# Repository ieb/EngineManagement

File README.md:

# Engine Management 

In July 2021 my boat was hit by lightning. The Volvo Penta D2-40 MDI unit that manages the Engine, a Volvo Penta D2-40F failed badly leaving the starter motor engaged and nearly causing an engine fire.

# Main control board

Update 20240417: In service, no issues after 3 years.

(see pcb/EngineManagementSimpleWithRelays.sch )

This project is based on the standard wiring for the core engine which is a Perkins 100. In that form the engine is controlled by switches, relays and a few flyback diodes. The only part of the original engine control that survived the strike was the Volvo Penta buttons, so those are used by a control board with pnp transistors driving relays triggered by the original buttons pulling the base of the pnp to ground. PushOn/PushOff is provided by a latching relay unit based on a LED control chip that draws a few uA when off. The control circuit draws 0.5A max and is protected by a 5A fuse and 600W TVS which will blow the fuse in the event of a voltage surge.

The main relays for Start, Stop, Glow and aux are all standard iso 40A automotive relays, each circuit fused with a suitable fuse. 

There are basic alarms for oil pressure, charge and temperature with the temperature alarm using a differential op amp with high gain adjusted to turn on a pnp at a set temperature. These all drive a buzzer with LEDs to indicate the alarm. 

A standard Tachometer sensing from the alternator W+ provides rev and engine hours. These are almost disposable being 30 GBP on eBay from many sources, all 85mm same as the Volvo Penta Tachometer.

## Mosfet alternative

Update 20240417: The PCB was prototyped, but never put into service since the relay based control board has proved 100% reliable and in service for 3 years. This section is for reference.

Although the original MDI failed due to the MOSFETs going short circuit, and in this respect relays may be more robust, it should be possible to protect MOSFETs or at least fail safe.

A 1.5KW TVS (eg SMCJ14A) with a 14.0V revers standoff, 15.6V minimum breakdown will conduct 5A@16V, 10A@18V and 40A@20V, which makes it viable as protection for excessive voltages upto 40A current, aiming to blow a fuse at above those voltages. Each mosfet needs its own TVS + suitably sized fuse or breaker. In the event of a strike or surge the TVS will short and blow the fuse before damage is done even if the MOSFET is shorted. It wont work for currents greater than 40A without exceeding the max Vds voltage of the MOSFET below.

A SI7137DP-T1-GE3 has an on resistance of 0.0016 Ohms and will dissipate < 640mW for 20A when fully on. It, unfortunately has a Max Vds of 20V and Vgs of 12v so needs protection, but provided its protected represents a robust solution as a high level switch. 

In the relay board on/off was provided by a eBay relay board which used a LED controller. To keep the number of daughter boards to a minimum and save space this is replaced by a MAX15054 on-off controller driving a N-Channel mosfet which when turned on draws the gate of one of the SI7137's to near zero turning it fully on. The same N-Channel mosfet enables P-Channel mosfets connected to the gates of other SI7137s. When the VP buttons are pressed the gates of these mosfets are dragged down to 0v turning them on, and since the N-Channel mosfet is conducting the gate of the respective SI7137 is also dragged to 0v switching that mosfet on. All P-Channel gates are pulled to +ve, and all N-Channel gates are pulled to 0v. The SI7137 has a max source gate voltage of 12v and so a 10v zener with forward diode ensures that never gets over 11.5v. 

Simulations indicate that the power dissipation in the SI7137 at 20A is 2.5W, so a pair are used for the glow plugs. At 8A for the start and stop solenoids power dissipation is closer to 500mW. Board cooling pads are used, although it might be necessary to add chip heat sinks.

Since the SI7137 are 1/10th the size of the relays, the switching circuit and NMEA2000 interface controller will all fit onto a single 10cm x 15cm board (which is the size I have in stock).

All of the silicon components were available at Farnell except the SI7137's which were ordered from Mouser, airmailed from California. For some reason RS in the UK had no stock of any mosfets.

see pcb/EngineManagementWithMosfets.sch which includes a sub-sheet of the NMEA interface. There are LTSpice simulations in pcb/simulations/ of the mosfet layout confirming transient behavior, currents and power dissipation.

Since its likely that when there is a voltage spike something on the board will blow, assuming this board works, I'll probably make a batch and keep a few spares onboard the boat.

# NMEA2000 Interface

Update 20240417: In service, minor issues after 3 years, mostly surrounding message frequency and how to some parameters to display on standard instruments.

(see pcb/EngineManagement.sch)

The standard MDI talks J1939 which is the Diesel engine CAN standard protocol. Normally this communicates with other Volvo Penta instruments, but in my case this was only the Tachometer. The J1939 Volvo Penta Tachometer did not survive the strike. The CAN bus interface was destroyed, even though there was an attempt to protect if from surges. At over 500 GBP to replace, I decided to stick with the non J1939 tachometer from eBay. For details on how to drive J1939 see the main_deprecated.cpp file. Volvo Penta service technicians probably query the MDI for fault codes, but for owners there is limited benefit where the only unit is a tachometer or basic instruments.

Once I discovered the VP Tachometer was not repairable, a separate mechanical diesel to NMEA2000 board was designed and built around an Arduino Pro Mini (Atmel 328p MCU), MCP2515 CAN controller board and some passive components. There is just enough space on 328p to hold the code and run the controller and the data collected and emitted can be displayed on any NMEA2000 instrument (eg Raymarine e7 MFD).

Component cost of the boards is probably less than 30 GBP, hence spares boards can be carried and in the worst case the engine can be controlled manually.

Replacing the blown VP parts with OEM parts would have been 1500 GBP with a further 1500 GBP required for the spare set, safe in the knowledge that a EM pulse from a near strike would result in precisely the same failure and risk of engine fire.

## NMEA2000 Messages

A D-2/40 is not exactly performance. Its not going to rev up quickly and so periods of 100ms are not really necessary for rapid engine. Same with temperatures which are really not going to change that fast. 5s is plenty fast enough.  10s is too long and most instruments treat this as no data sent.

* pgn 127488 rapid engine, 500ms
* pgn 127489 dynamic engine 1s  oil temperature == alternator temperature.
* pgn 127505 tank level 5s, instance 0 fuel type 0 diesel 
* pgn 130316 temperatures 5s,  instance/source 0/14=Exhaust, 1/3=EngineRoom, 2/15=Alternator.
* pgn 127508L battery voltage 1s, instance 0=engine battery, voltage only. instance 2=Alternator, voltage and temperature

The main battery as its now LiFePO4 with a serial to BLE module providing very detailed information. A CAN interface to this could be implemented, but the standard android app gives more than enough information and is lower power.  The original battery sensor mechanism didnt work well due to slight differences in -ve potential at the battery terminals. Hence the N2K interface only monitors Engine Battery and Alternator voltages. With a LiFeP04 battery, alternator temperature has become more important. Alternator load is controld via a Sterling A2B 120A converter which actively monitors and protect the alternator from excessive load.

# Sensors

The standard  VP flywheel pickup produces 415Hz 20V pk2pk puses with sharp edges at idle, however the signal is noisy and so it needs to be conditioned. A Schmidt trigger using an OpAmp set up positive feedback to reduce hysteresis. The positive input uses a RC network acting as a low pass filter reducing the sensitivity as the rpm rises, eliminating high frequencies ( > 10KHz). On the negative a RC network smooths the input voltage to find the mean allowing automatic offset compensation. The time period constant of the -ve input is >> than the +ve.  The inputs are via 22K resistors with the voltage measured over 100K. There are 2 chopper diodes to limit the input voltage to no more than 1V.

Using a 358 opamp with 5V supply the square wave out is 3.7V high and 0.7v low, which is just enough (3.5v being logic high), 1.5 below Vcc isn't great for an OpAmp, however 3v is high on an Arduino.

The frequency is measured by timing 10 pulses using micros().

The previous attempt without a Schmidt Trigger failed to work reliably due to noise.

The standard VP oil pressure switch is a simple switch that closes when the oil pressure drops below a threshold.

The standard VP coolant temperature sensor is identical to almost every other coolant sensor, with about 1743R at 0C and 22R at 120C. When about 33R (105C adjustable) is measured the alarm is triggered.

The charge alarm uses the voltage across the resistor supplying current into the alternator excitation coil, analogous to the charge light in cars long before there were computers.

The NMEA2000 interface board also measures fule level (0R-190R), battery voltage, alternator voltage, and 3 NCT inputs. Inputs are protected with capacitors and 100K resistors to limit current.

# Outputs

The relay board provides outputs for starter motor, stop solenoid, glow plugs and aux 12v.

The NMEA2000 board provides NMEA2000 messages.

# Connections.

The VP wiring loom has largely been replaced except for the connection to the VP buttons. Most of the original wiring loom was melted by the starter motor, but the rest was strapped tightly to the engine risking shorts when it melted.

The control box will be mounted outside the engine bay where temperatures are considerably lower (typically < 30C vs often > 85C next to the engine).

# Code

Code is all in main.cpp rather than a classes since there is little to it and I needed tight control over memory usage (less risk of hidden bloat). NMEA support uses 

	https://github.com/ttlappalainen/NMEA2000.git
	https://github.com/ttlappalainen/NMEA2000_mcp.git
	https://github.com/ttlappalainen/CAN_BUS_Shield.git

however there are some patches required, see src/*.patch. 
src/CAN_BUS_Shield.patch. The SPI clk was heavily distorted at 8MHz with a Pro Mini so I dropped the SPI to 1MHz to get a clean clk square wave. 

src/NMEA2000-library.patch The memory savings (see NMEA2000_CompilerDefns.h) which are required to run on a 382p dont compile without this patch. Additionally there I needed feedback on serial of failed packets without enabling all packet output.

Both patches must be applied if pulling fresh dependencies. 

# Memory usage

Building .pio/build/pro16MHzatmega328/firmware.hex
Advanced Memory Usage is available via "PlatformIO Home > Project Inspect"
RAM:   [==        ]  18.4% (used 377 bytes from 2048 bytes)
Flash: [========= ]  89.4% (used 27458 bytes from 30720 bytes)

If debugging of the sensors is enabled, then NMEA2000 output may have to be disabled to get the code to fit into FLASH. No problems seen with RAM at the moment, but it hasnt been tested on a live NMEA2000 bus yet.

## Update on memory.

Memory usage has proved a problem. The NMEA2000 library was designed for chips with more memory than a Pro mini and although it will run, it runs out of stack and heap when dealing with ISO Reqeusts, causing the cpu to lock up or crash. It is possible to greatly reduce memory usage by limiting buffer sizes but this truncates the responses ot the ISO requests. I think the underlying problem is that the NMEA2000 library uses temporary buffers allow it to use interrupts and to support TP packets.

So, the code is now switched to a smaller SNMEA2000 library. This only uses an 8 byte buffer for sending and is written to load that buffer, sending when full. It supports standard packets and fast packet messages. It doesn't support interrupts and is a lot simpler. 

Building with debug enabled all in ram gives
RAM:   [===       ]  32.2% (used 659 bytes from 2048 bytes)
Flash: [====      ]  37.4% (used 11492 bytes from 30720 bytes)

Initial tests indicate 1292 bytes ram available at all times when running, compared to the < 60 bytes reported with the smallest viable NMEA2000 configuration. Most of the implementation is informed by the NMEA2000 code and functionality for each use is by extension only. To reduce the work load on a polling only interface to the MCP2515 message filters are implemented on receive. It only supports a MCP2515 over SPI and will only run on an AVR based chip as it assumes little endian.

The code has, or is being verified talking to a ESP32 + MCP2562 running the NMEA2000 device analyzer.

# Changes

* 20240417  Reduced the periods for battery and fuel to 5s from 10s as N2K instruments were showing -.- periodically.
* 20240417  Output Alternator temperature to Engine Oil Temp and a dedicated "battery" (no 2) for display. Oddly no standard PGN for an DC alternator available.

# Todo/Status Relay Board

[x] Build prototype PCB and populate.
[x] Test on/off sequence.
[x] Test 20x4 I2C display.
[x] Test port extender. - discovered Can board back powers 5v switched line, added blocking diode.
[x] Connect 8 way relay board and test.
[x] Verify CAN board working.
[ ] Connect test harness sensors and test.
[FAIL] Connect VP Taco and test with simulated engine - the VP Taco is blown internally, CanH at 5V, CanL and 0V. Inside three is a large Asic which looks like it directly controls the Can bus. Very unlikely to be 
able to repair. Google for the numbers turns up no chips, and none of the other chips are CAN related.

[x] Design build and test simple relay controller unit with no MCU
[x] Design build NMEA2000 controller board
[x] Test NCT readings,  - adjusted to 4.7K top R and rebuilt NTC table from base equations.
[x] Test coolant readings - tested with fake NTC sensor wiring, need full test on real sensor
[x] Test fuel level readings
[x] Test voltage readings
[x] Test coolant with variable voltage.
[x] Test RPM with signal generator
[x] Test NMEA2000 output
[x] install
[x] Test output on MFD, all working except Charge alarm sounds all the time and RPM sensor is unreliable.
[x] Fix RPM sensor, using Schmidt trigger
[x] (disabled) Fix charge sensor, adjust resistors or disable.
[x] Adjust temperature sensor
[x] calibrate ADCs, or at least check they are correct.
[x] Test again.
[x] Install check RPM with strobe
[x] Fix fuel and voltage periods, 10s too long for N2K instruments, dropped to 5s.
[x] Output alternator temperature as oil temp, dedicated "battery" instance 2.

# Todo Status Mosfet board

This has been put on hold as the relay board works well other than the charge and temperature alarms whcih are too sensitive. Same mosfets have been used for a high current remote switch and appear to produce almost zero heat dissipation.

[x] Simulate everything in LTSpice
[x] Layout PCB
[ ] Mill prototype
[x] Order Silicon
[ ] Build prototype
[ ] Test on/off
[ ] Test other buttons and circuits, under load ideally.
[ ] Test warning circuits
[ ] Test sensors
[ ] Test NMEA2000 output
[ ] Install
[ ] Test running
[ ] Order boards and build spares.

# CanDrivers

# AVR -> MCP2515 -> TJA1050

TJA1050 runs on 5V but can take 3 or 5v logic in.
MCP2515 will run on 3v or 5v On 3v it will need a 1K/10K divider to take TJA1050 out from 3.6v to 3.3v

Scope output for this setup on 5V is very clean

# ESP -> TJA1050

TJA1050 runs on 5v with a divider on RX out to take Vrxh to 3.3v, may be easier than a MCP2562, although the output from a MCP2562 is not nearly as clean.

This setup works. Output is very clean, however the mean voltage is sensitive to the 5V supply being exactly 5V.

# Pi -> MCP2515 -> TA1050

Same as 3v AVR 3v.
Would also need a RTC, DS3231  with a LI charger TP4056
Not done as was able to fit everything I wanted into a ESP32 running a http server which draws < 40mA when not transmitting on WiFi, see CanDiagnose project.

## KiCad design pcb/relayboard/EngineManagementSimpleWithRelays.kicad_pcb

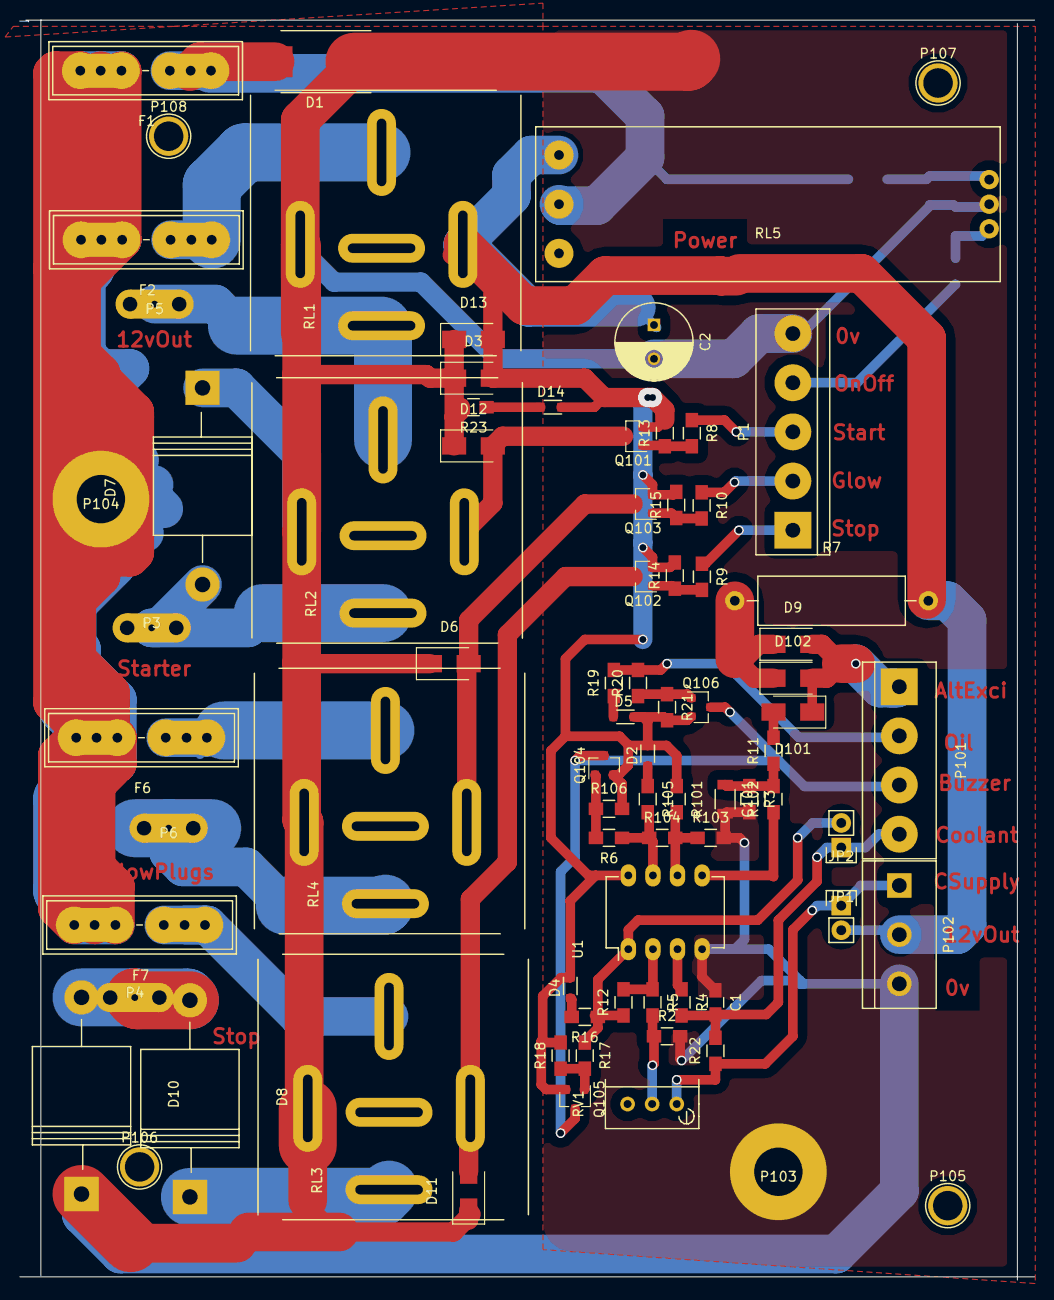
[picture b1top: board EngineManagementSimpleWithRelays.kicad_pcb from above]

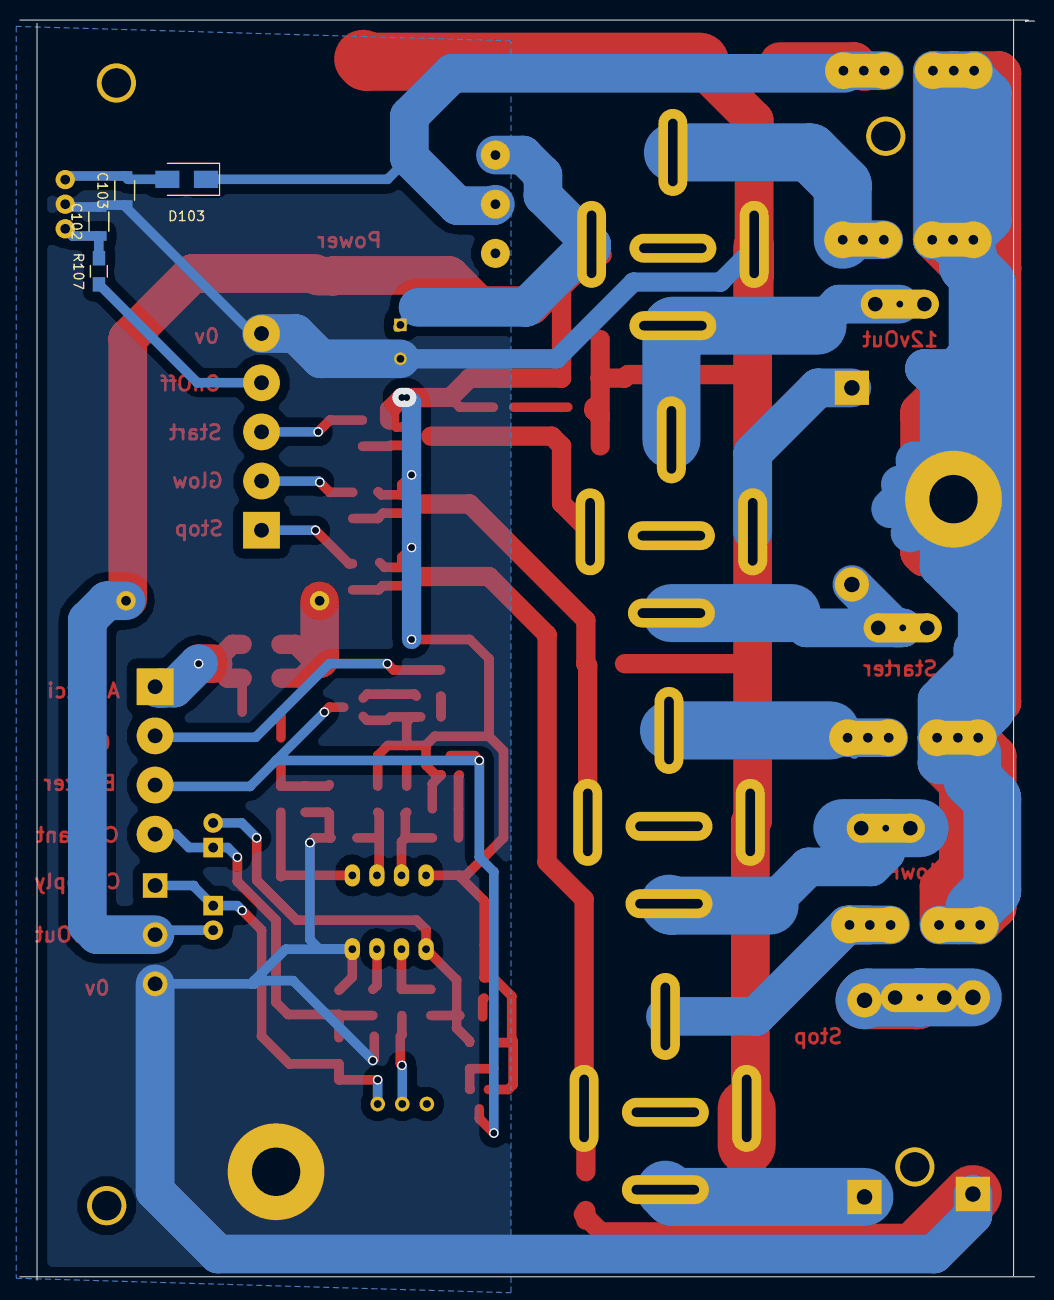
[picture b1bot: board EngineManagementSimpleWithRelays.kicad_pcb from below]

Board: 2 copper layers, 104.8 x 130.2 mm, 83 parts (4 on the bottom side), 46 nets.

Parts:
C1: 10nF; C_0805_HandSoldering
C2: 100uF; C_Radial_D8_L11.5_P3.5
C101, C103: 1uF; C_1206
C102: 100nF; C_1206
D1: SMBJ30CA-TR TSV; DO-214AB_Handsoldering
D2: ChargeWarn; D_0805
D3, D9, D102, D103: S1JL 1A 40V; D_SMA_Standard
D4: TempWarn; D_0805
D5, D14: OilWarn; D_0805
D6, D11, D12, D13: S1JL 1A 600V; D_SMA_Standard
D7: 5A 600V; Diode_P600_Horizontal
D8, D10: 10A 600V; Diode_P600_Horizontal
D101: SlJL 1A 40V; D_SMA_Standard
F1: FUSE 5A; BladeFuse-CarType
F2, F6: FUSE 30A; BladeFuse-CarType
F7: FUSE 15A; BladeFuse-CarType
JP1: UseSensorAlarm; Pin_Header_Straight_1x02
JP2: Use12vSupply; Pin_Header_Straight_1x02
P1: VPButtons; bornier5
P3: StarterSolenoidT30; CrimpBlade
P4: StopSolenoid; CrimpBlade
P5: 12VSwitchedPower; CrimpBlade
P6: GlowPlugs; CrimpBlade
P101: CONN_4; bornier4
P102: CONN_3; bornier3
P103: 0v; M5Bolt
P104: Battery+; M5Bolt
P105, P106, P107, P108: mount; 1pin
Q101, Q102, Q103, Q104, Q105, Q106: BC807-40; SOT-23
R2: 330R; R_0805_HandSoldering
R3: 1M; R_0805_HandSoldering
R4, R5, R6, R13, R14, R15, R17, R21, R101: 10K; R_0805_HandSoldering
R7: 10R; Resistor_Horizontal_RM20mm
R8, R9, R10, R18, R20, R106: 2.2K; R_0805_HandSoldering
R11, R16, R19, R22, R23, R102, R105, R107: 1K; R_0805_HandSoldering
R12: 10M; R_0805_HandSoldering
R103: 22K; R_0805_HandSoldering
R104: 100K; R_0805_HandSoldering
RL1: EnginePower; AutomotiveRelay35A
RL2: EngineStart; AutomotiveRelay35A
RL3: EngineStop; AutomotiveRelay35A
RL4: GlowPlugs; AutomotiveRelay35A
RL5: LatchingRelay
RV1: 10K; Potentiometer_Bourns_3296W_3-8Zoll_Inline_ScrewUp
U1: LM358; DIP-8_W7.62mm_LongPads

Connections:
12vSwitched: C2.1, D2.1, D3.2, D4.1, D5.1, D13.2, D14.1, JP2.2, P102.2, Q101.2, Q102.2, Q103.2, Q104.2, Q105.2, Q106.2, R7.2, R13.2, R14.2, R15.2, R18.2, R21.2, R101.1, R106.2, RL1.86, RL5.6, U1.8
AlternatorExcitation: D9.2, D101.1, D102.2, P101.1
Battery+: F1.2, F2.2, F6.2, F7.2, P104.1
BatteryFused5A: D1.2, D103.1, F1.1, RL5.4
Buzzer: P101.3, Q104.3, Q105.3, Q106.3
CoolantSensorSupply: JP2.1, P102.1, R22.1, RV1.1
CoolantTemp: C1.2, JP1.1, P101.4, R4.2, R22.2
GND: C1.1, C2.2, C101.2, C102.2, C103.1, D1.1, D3.1, D6.1, D7.1, D10.1, D11.1, D12.1, D13.1, P1.5, P102.3, P103.1, R2.2, R3.2, R23.2, R103.2, RL1.85, RL2.85, RL3.85, RL4.85, RL5.3, U1.4
GlowBtn: P1.2, R10.1
GlowCoil: D6.2, Q103.3, RL4.86
GlowPlugs: P6.1, RL4.87
unnamed: C101.1, R3.1, R11.1, R102.2
unnamed: C102.1, R107.2, RL5.2
unnamed: C103.2, D103.2, RL5.1
unnamed: D2.2, R105.1
unnamed: D4.2, R16.2
unnamed: D5.2, R19.1
unnamed: D8.1, RL3.87
unnamed: D14.2, R23.1
unnamed: D101.2, R11.2
unnamed: D9.1, D102.1, R7.1
unnamed: F2.1, RL1.30
unnamed: P5.1, RL1.87, RL2.30
unnamed: F6.1, RL4.30
unnamed: F7.1, RL3.30
unnamed: JP1.2, R12.1, R16.1, R17.1, U1.1
unnamed: Q101.1, R8.2, R13.1
unnamed: Q102.1, R9.2, R14.1
unnamed: Q103.1, R10.2, R15.1
unnamed: Q104.1, R6.2, R106.1
unnamed: Q105.1, R17.2, R18.1
unnamed: Q106.1, R20.1, R21.1
unnamed: R2.1, R5.2, RV1.2
unnamed: R4.1, U1.3
unnamed: R5.1, R12.2, U1.2
unnamed: R101.2, R103.1, R104.2, U1.6
unnamed: R102.1, U1.5
unnamed: R6.1, R104.1, R105.2, U1.7
OilSwitch: P101.2, R19.2, R20.2
OnOffBtn: P1.4, R107.1
StartBtn: P1.3, R8.1
StartCoil: D12.2, Q101.3, RL2.86
StarterSolenoidT30: D7.2, P3.1, RL2.87
StopBtn: P1.1, R9.1
StopCoil: D11.2, Q102.3, RL3.86
StopSolenoid: D8.2, D10.2, P4.1

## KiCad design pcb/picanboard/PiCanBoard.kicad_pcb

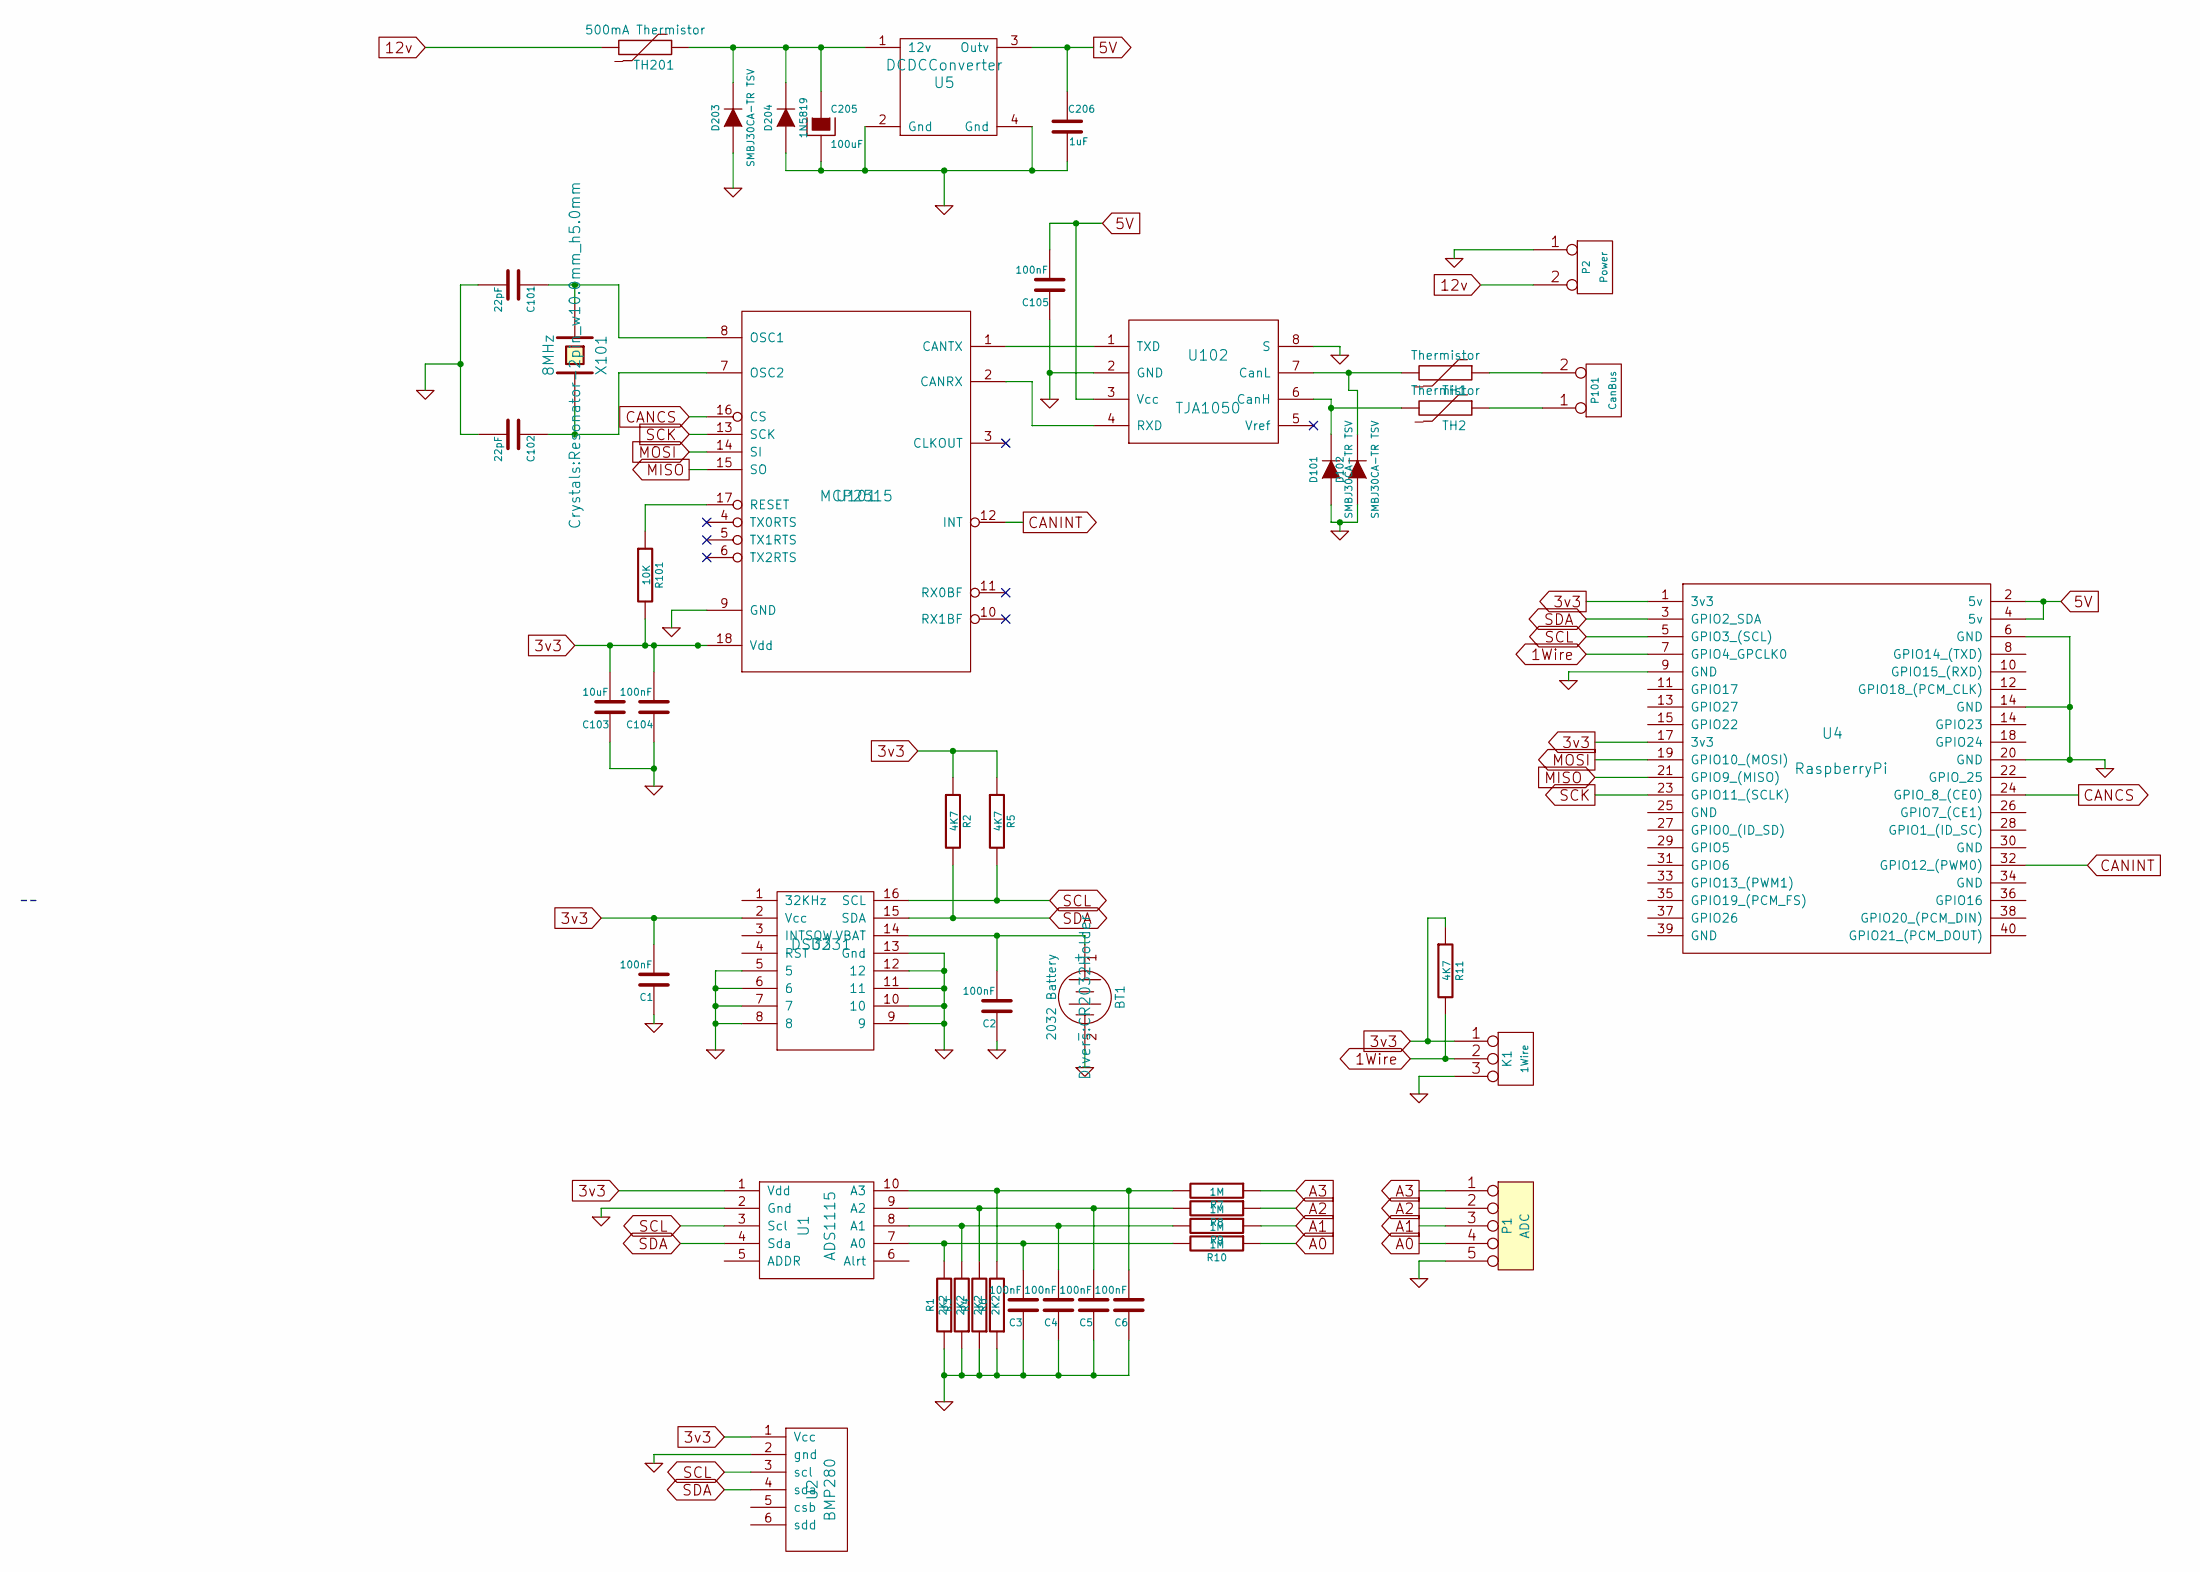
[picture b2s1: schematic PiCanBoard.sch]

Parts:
BT1: 2032 Battery; CR2032Holder
C1, C2, C3, C4, C5, C6, C104, C105: 100nF; C_0805_HandSoldering
C101, C102: 22pF; R_0603_HandSoldering
C103: 10uF; R_1206_HandSoldering
C205: 100uF; C_1210_HandSoldering
C206: 1uF; C_1210_HandSoldering
D101, D102, D203: SMBJ30CA-TR TSV; DO-214AB_Handsoldering
D204: 1N5819; DO-214AB_Handsoldering
K1: 1Wire; bornier3
P1: ADC; bornier5
P2: Power; bornier2
P101: CanBus; bornier2
R1, R3, R4, R6: 2K2; R_0805_HandSoldering
R2, R5, R11: 4K7; R_0805_HandSoldering
R7, R8, R9, R10: 1M; R_0805_HandSoldering
R101: 10K; R_0805_HandSoldering
TH1, TH2: Thermistor; R_1210
TH201: 500mA Thermistor; Resistor_Horizontal_RM7mm
U1: ADS1115
U2: BMP280
U3: DS3231; SOIC-16W_7.5x10.3mm_Pitch1.27mm
U4: RaspberryPi; PiZeroW
U5: DCDCConverter; DC-DC-Converter
U101: MCP2515; SOIC-18W_7.5x11.6mm_Pitch1.27mm
U102: TJA1050; SOIC-8_3.9x4.9mm_Pitch1.27mm
X101: 8MHz; Resonator-2pin_w10.0mm_h5.0mm

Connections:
1Wire: K1.2 (PM), R11.2, U4.7 (GPIO4_GPCLK0)
3v3: C1.2, C103.2, C104.2, K1.1, R2.1, R5.1, R11.1, R101.2, U1.1 (Vdd), U2.1 (Vcc), U3.2 (Vcc), U4.1 (3v3), U4.17 (3v3), U101.18 (Vdd)
5V: C105.2, C206.1, U4.2 (5v), U4.4 (5v), U5.3 (Outv), U102.3 (Vcc)
12v: P2.2 (PM), TH201.2
A0: P1.4, R10.1
A1: P1.3, R9.1
A2: P1.2, R8.1
A3: P1.1, R7.1
CANCS: U4.24 (GPIO_8_(CE0)), U101.16 (CS)
CANINT: U4.32 (GPIO12_(PWM0)), U101.12 (INT)
GND: BT1.2 (-), C1.1, C2.1, C3.1, C4.1, C5.1, C6.1, C101.2, C102.2, C103.1, C104.1, C105.1, C205.2, C206.2, D101.1 (A), D102.1 (A), D203.1 (A), D204.1 (A), K1.3, P1.5, P2.1, R1.1, R3.1, R4.1, R6.1, U1.2 (Gnd), U2.2 (gnd), U3.5, U3.6, U3.7, U3.8, U3.9, U3.10, U3.11, U3.12, U3.13 (Gnd), U4.6 (GND), U4.9 (GND), U4.14 (GND), U4.20 (GND), U5.2 (Gnd), U5.4 (Gnd), U101.9 (GND), U102.2 (GND), U102.8 (S)
MISO: U4.21 (GPIO9_(MISO)), U101.15 (SO)
MOSI: U4.19 (GPIO10_(MOSI)), U101.14 (SI)
unnamed: BT1.1 (+), C2.2, U3.14 (VBAT)
unnamed: C3.2, R1.2, R10.2, U1.7 (A0)
unnamed: C4.2, R3.2, R9.2, U1.8 (A1)
unnamed: C5.2, R4.2, R8.2, U1.9 (A2)
unnamed: C6.2, R6.2, R7.2, U1.10 (A3)
unnamed: C101.1, U101.8 (OSC1), X101.1
unnamed: C102.1, U101.7 (OSC2), X101.2
unnamed: C205.1, D203.2 (K), D204.2 (K), TH201.1, U5.1 (12v)
unnamed: D101.2 (K), TH2.2, U102.6 (CanH)
unnamed: D102.2 (K), TH1.2, U102.7 (CanL)
unnamed: P101.1, TH2.1
unnamed: P101.2 (PM), TH1.1
unnamed: R101.1, U101.17 (RESET)
unnamed: U101.1 (CANTX), U102.1 (TXD)
unnamed: U101.2 (CANRX), U102.4 (RXD)
SCK: U4.23 (GPIO11_(SCLK)), U101.13 (SCK)
SCL: R5.2, U1.3 (Scl), U2.3 (scl), U3.16 (SCL), U4.5 (GPIO3_(SCL))
SDA: R2.2, U1.4 (Sda), U2.4 (sda), U3.15 (SDA), U4.3 (GPIO2_SDA)

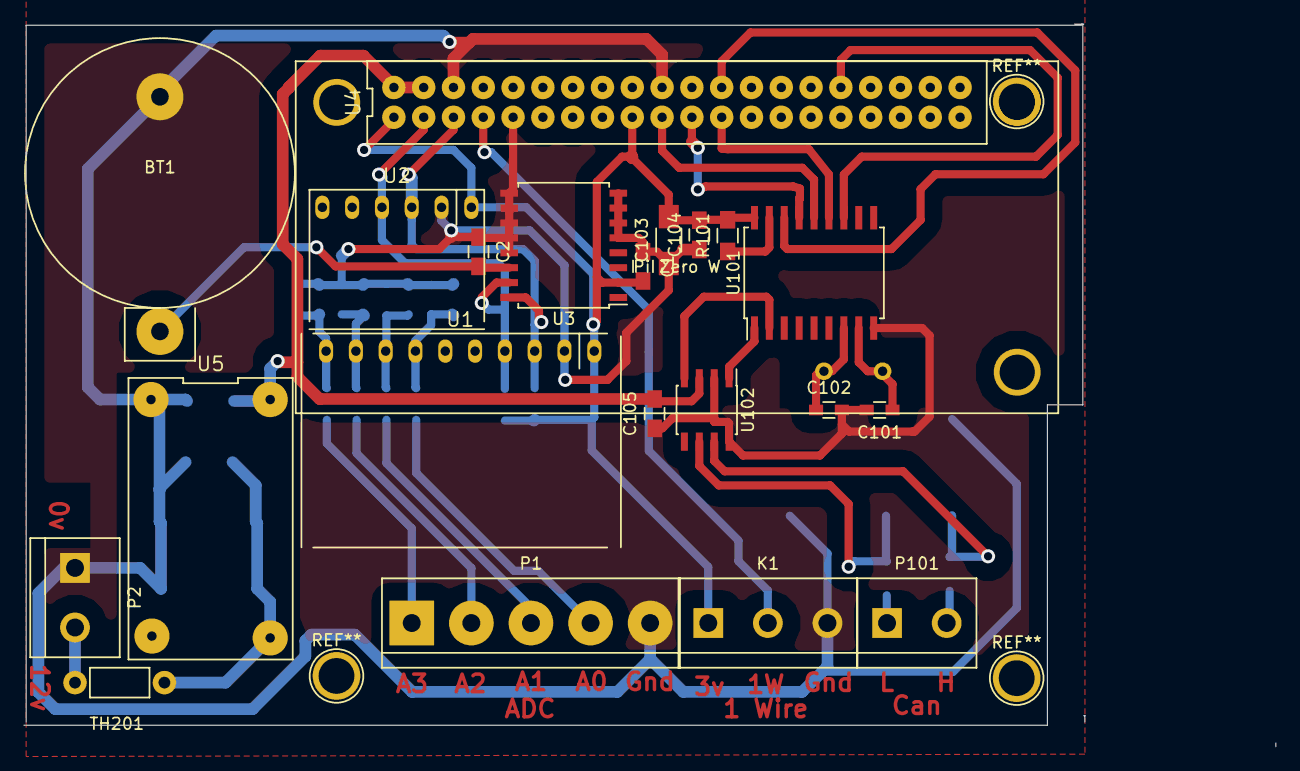
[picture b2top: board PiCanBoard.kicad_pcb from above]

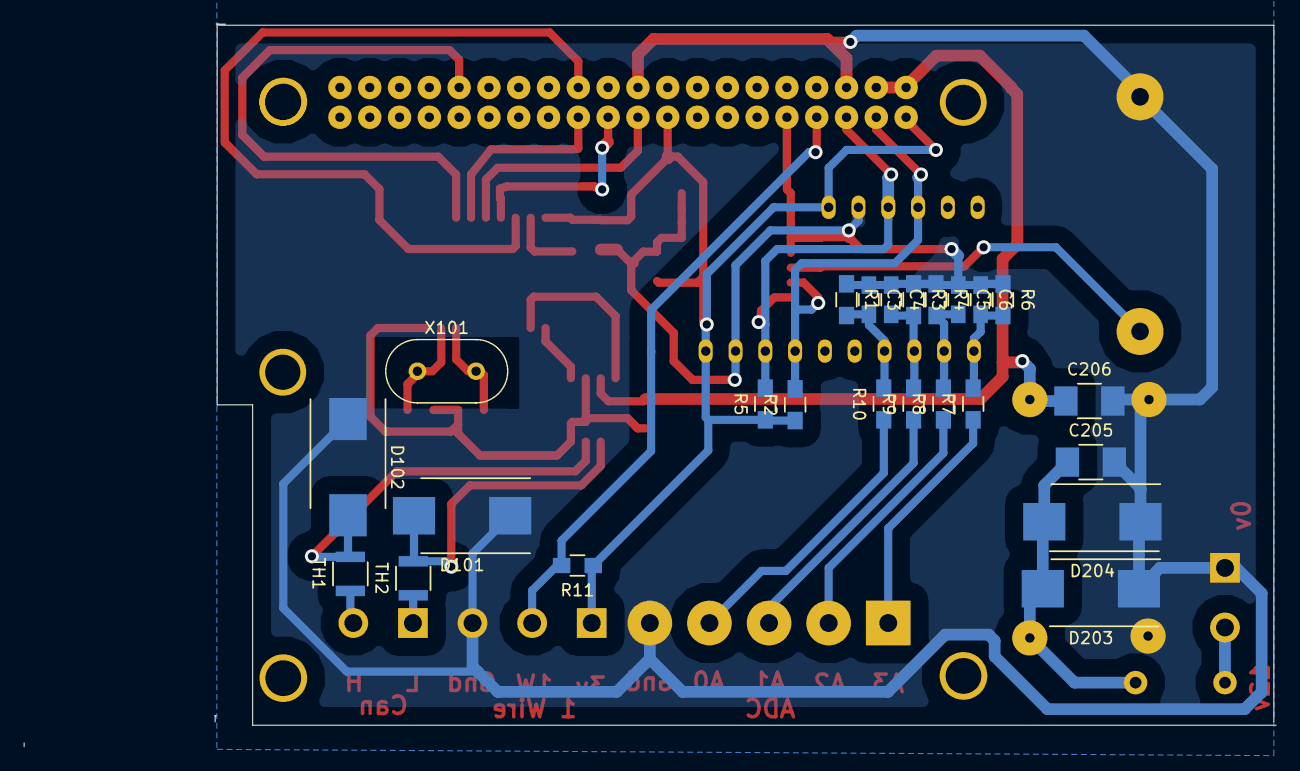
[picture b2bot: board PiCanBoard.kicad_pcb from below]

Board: 2 copper layers, 106.7 x 61.6 mm, 45 parts (24 on the bottom side), 31 nets.

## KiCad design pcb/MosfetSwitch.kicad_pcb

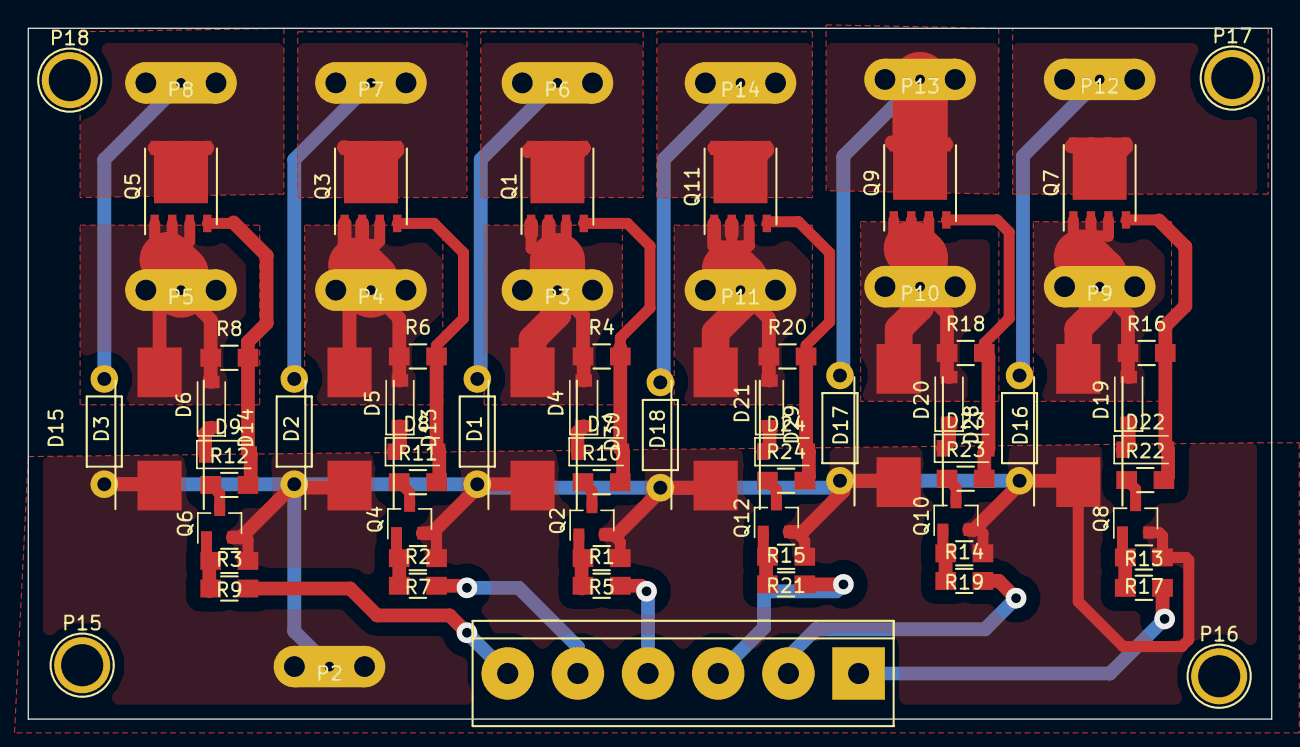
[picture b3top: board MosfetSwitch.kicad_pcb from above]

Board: 2 copper layers, 90.0 x 50.0 mm, 78 parts (0 on the bottom side), 43 nets.

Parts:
D1, D2, D3, D16, D17, D18: SMBJ30CA-TR TSV; DO-214AB_Handsoldering
D4, D5, D6, D19, D20, D21: ZENER; D_SOD-123
D7, D8, D9, D22, D23, D24: 1N4001; D_SOD-123
D13, D14, D15, D28, D29, D30: 1N4001; Resistor_Horizontal_RM7mm
P1: ToSwitches; bornier6
P2: 0v; CrimpBlade
P3: CH3In; CrimpBlade
P4: CH2In; CrimpBlade
P5: CH1In; CrimpBlade
P6: Ch3Out; CrimpBlade
P7: Ch2Out; CrimpBlade
P8: Ch1Out; CrimpBlade
P9: CH6In; CrimpBlade
P10: CH5In; CrimpBlade
P11: CH4In; CrimpBlade
P12: Ch6Out; CrimpBlade
P13: Ch5Out; CrimpBlade
P14: Ch4Out; CrimpBlade
P15, P16, P17, P18: hole; 1pin
Q1, Q3, Q5, Q7, Q9, Q11: SI7137; Si7137PowerPak
Q2, Q4, Q6, Q8, Q10, Q12: BC817-40; SOT-23
R1, R2, R3, R4, R5, R6, R7, R8, R9, R13, R14, R15, R16, R17, R18, R19, R20, R21: 10K; R_0805_HandSoldering
R10, R11, R12, R22, R23, R24: 470R; R_0805_HandSoldering

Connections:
CH1_SWITCH: P1.6, R3.2
CH2_SWITCH: P1.5, R2.2
CH3_SWITCH: P1.4, R1.2
CH4_SWITCH: P1.3, R15.2
CH5_SWITCH: P1.2, R14.2
CH6_SWITCH: P1.1, R13.2
GND: D1.1, D2.1, D3.1, D13.1, D14.1, D15.1, D16.1, D17.1, D18.1, D28.1, D29.1, D30.1, P2.1, Q2.2, Q4.2, Q6.2, Q8.2, Q10.2, Q12.2, R5.1, R7.1, R9.1, R17.1, R19.1, R21.1
unnamed: D1.2, D4.2, P3.1, Q1.2, R4.1
unnamed: D2.2, D5.2, P4.1, Q3.2, R6.1
unnamed: D3.2, D6.2, P5.1, Q5.2, R8.1
unnamed: D4.1, D7.1
unnamed: D5.1, D8.1
unnamed: D6.1, D9.1
unnamed: D7.2, Q1.1, R4.2, R10.2
unnamed: D8.2, Q3.1, R6.2, R11.2
unnamed: D9.2, Q5.1, R8.2, R12.2
unnamed: D13.2, P6.1, Q1.3
unnamed: D14.2, P7.1, Q3.3
unnamed: D15.2, P8.1, Q5.3
unnamed: D16.2, D19.2, P9.1, Q7.2, R16.1
unnamed: D17.2, D20.2, P10.1, Q9.2, R18.1
unnamed: D18.2, D21.2, P11.1, Q11.2, R20.1
unnamed: D19.1, D22.1
unnamed: D20.1, D23.1
unnamed: D21.1, D24.1
unnamed: D22.2, Q7.1, R16.2, R22.2
unnamed: D23.2, Q9.1, R18.2, R23.2
unnamed: D24.2, Q11.1, R20.2, R24.2
unnamed: D28.2, P12.1, Q7.3
unnamed: D29.2, P13.1, Q9.3
unnamed: D30.2, P14.1, Q11.3
unnamed: Q2.1, R1.1, R5.2
unnamed: Q2.3, R10.1
unnamed: Q4.1, R2.1, R7.2
unnamed: Q4.3, R11.1
unnamed: Q6.1, R3.1, R9.2
unnamed: Q6.3, R12.1
unnamed: Q8.1, R13.1, R17.2
unnamed: Q8.3, R22.1
unnamed: Q10.1, R14.1, R19.2
unnamed: Q10.3, R23.1
unnamed: Q12.1, R15.1, R21.2
unnamed: Q12.3, R24.1
